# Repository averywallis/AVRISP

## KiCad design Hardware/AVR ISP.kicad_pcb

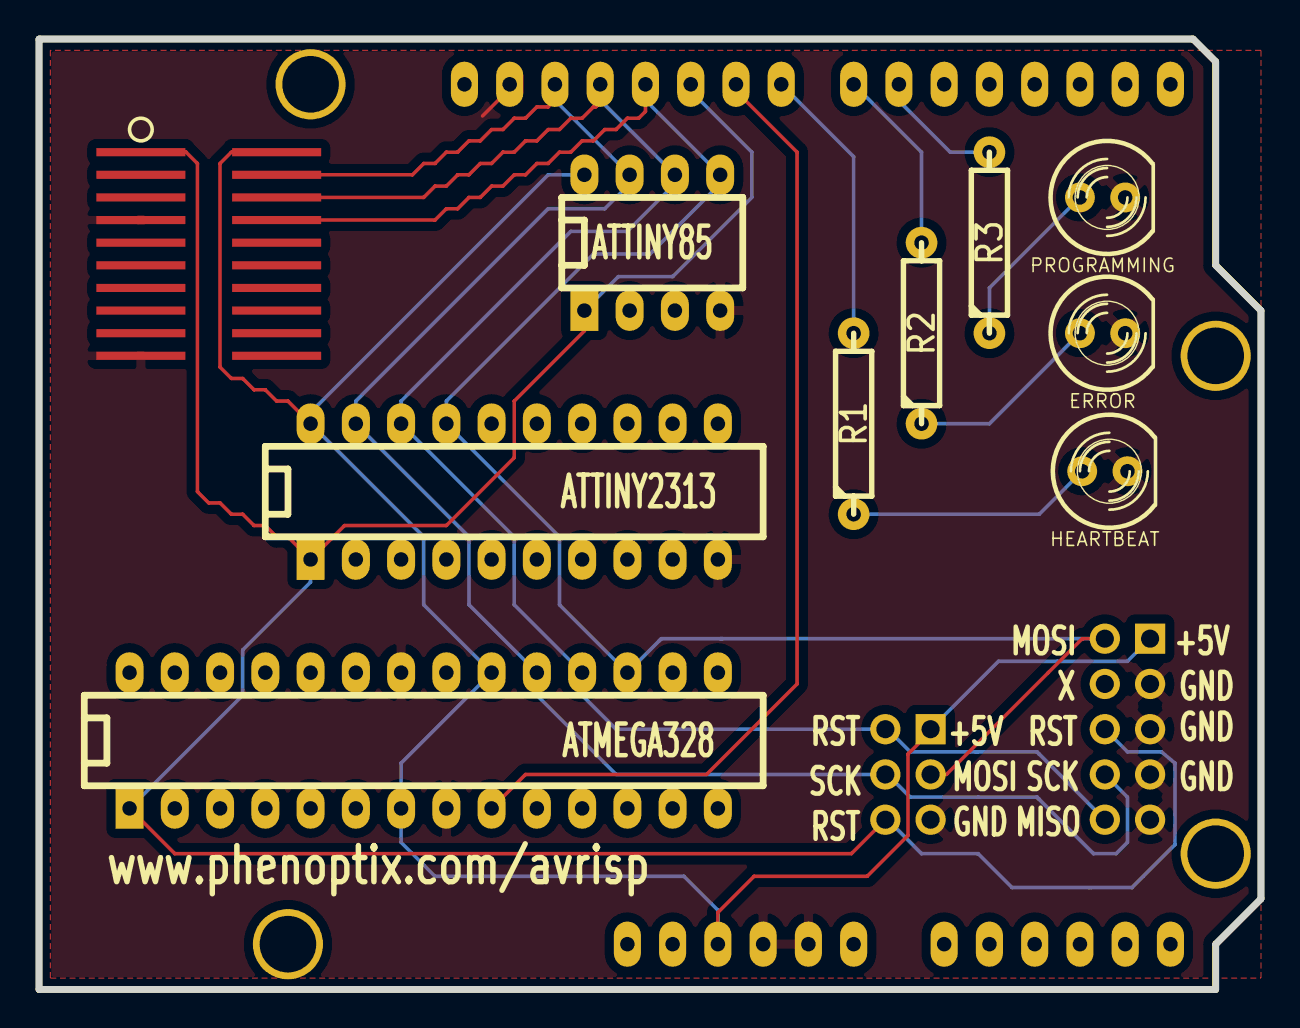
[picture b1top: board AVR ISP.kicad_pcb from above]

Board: 2 copper layers, 68.6 x 53.3 mm, 14 parts (0 on the bottom side), 13 nets.

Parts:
CON1: AVR-ISP-6; pin_array_3x2
CON2: AVR-ISP-10; PIN_ARRAY_5x2
D1: HEARTBEAT; LED-5MM
D2: ERROR; LED-5MM
D3: PROGRAMMING; LED-5MM
IC1: ATMEGA328; DIP-28__300_ELL
IC2: ATTINY2313; DIP-20__300_ELL
IC3: ATTINY85; DIP-8__300_ELL
R1, R2, R3: R; R4-LARGE_PADS
SHIELD1: ARDUINO_SHIELD
SOIC - 8: Test; SOIC20_Test
VAL: logoBigBackSilk

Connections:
+5V: CON1.2, CON2.2, IC1.7, IC1.20, IC2.20, IC3.8, SHIELD1.5V, SOIC - 8.20
GND: CON1.6, CON2.4, CON2.6, CON2.8, CON2.10, D1.2, D2.2, D3.2, IC1.8, IC1.22, IC2.10, IC3.4, SHIELD1.GND1, SHIELD1.GND2, SHIELD1.GND3, SOIC - 8.4, SOIC - 8.10
unnamed: CON1.1, CON2.9, IC1.18, IC2.18, IC3.6, SHIELD1.12, SOIC - 8.18
unnamed: CON1.4, CON2.1, IC1.17, IC2.17, IC3.5, SHIELD1.11, SOIC - 8.17
unnamed: CON1.3, CON2.7, IC1.19, IC2.19, IC3.7, SHIELD1.13, SOIC - 8.19
unnamed: R3.2, SHIELD1.6
unnamed: D3.1, R3.1
unnamed: R1.2, SHIELD1.8
unnamed: D1.1, R1.1
unnamed: R2.2, SHIELD1.7
unnamed: D2.1, R2.1
unnamed: IC1.9, SHIELD1.9
unnamed: CON1.5, CON2.5, IC1.1, IC2.1, IC3.1, SHIELD1.10, SOIC - 8.1

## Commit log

2020-01-07 Updated KiCad files

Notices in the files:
Hardware/AVR ISP.kicad_pcb:
CC BY-SA 3.0
